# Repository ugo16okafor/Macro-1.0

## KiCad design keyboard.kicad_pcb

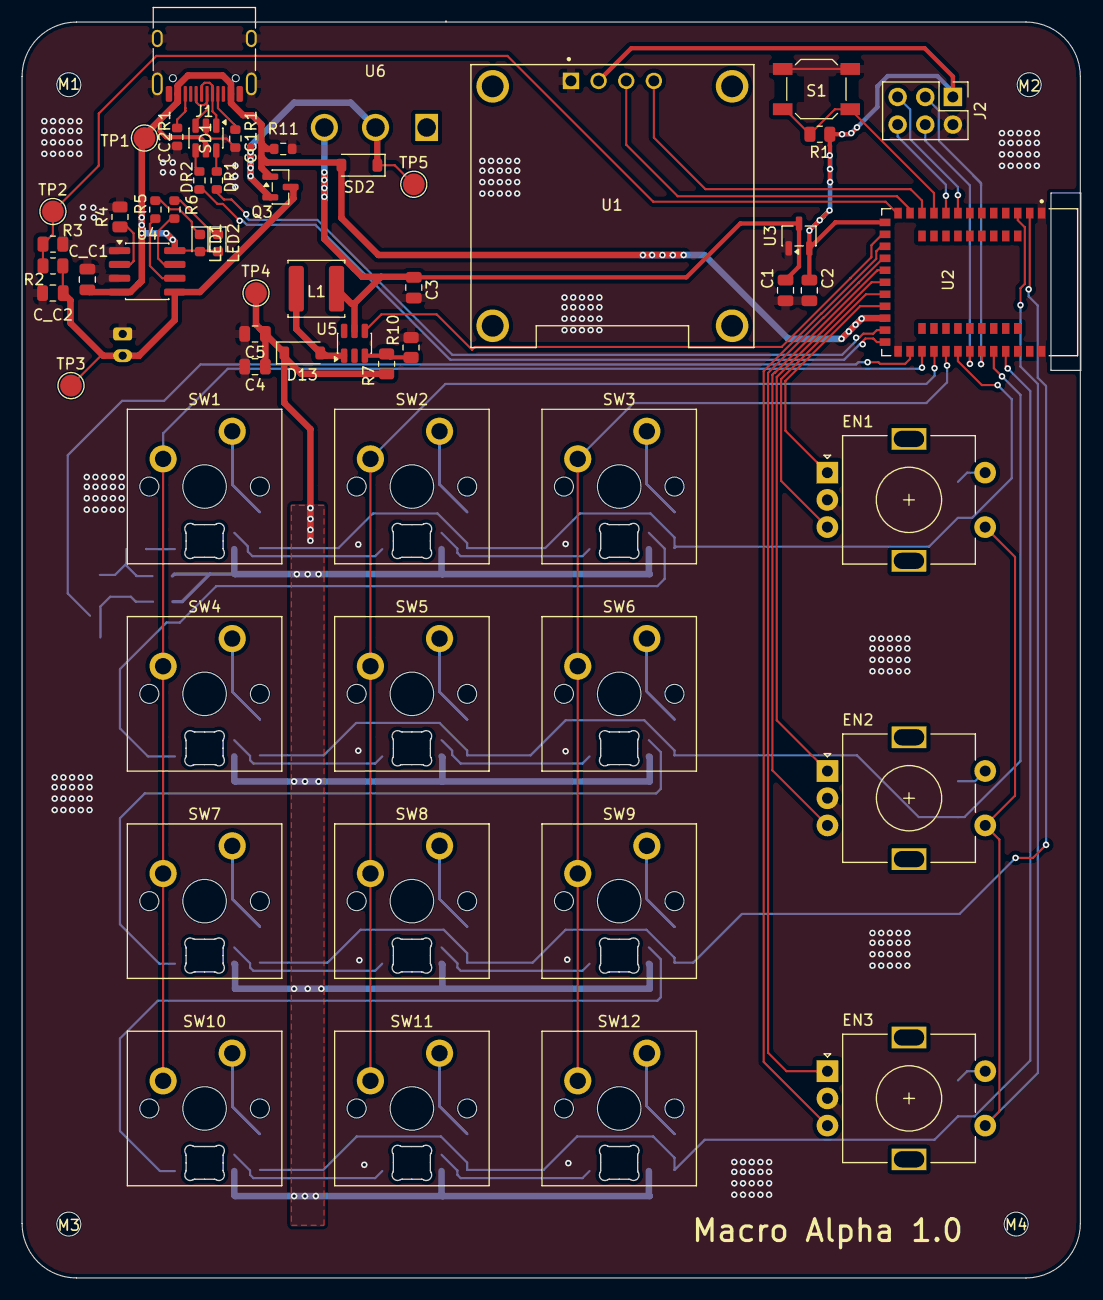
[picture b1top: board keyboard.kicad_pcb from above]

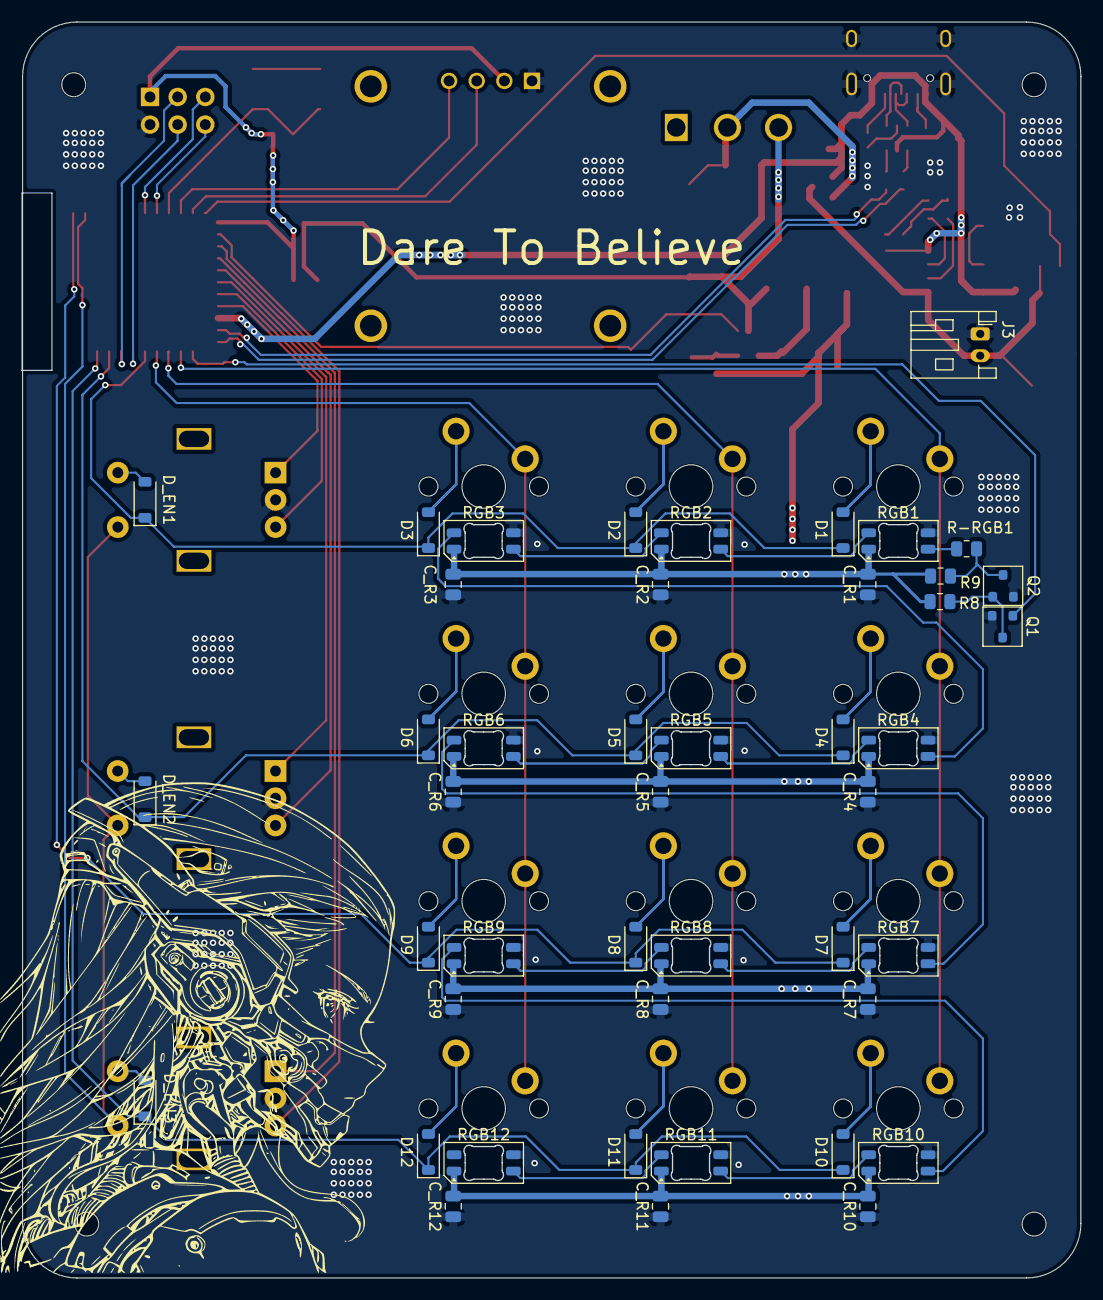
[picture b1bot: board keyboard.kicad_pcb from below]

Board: 2 copper layers, 97.3 x 115.4 mm, 105 parts (45 on the bottom side), 75 nets.

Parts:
C1, C2: 1uF; C_0805_2012Metric
C3, C5: 22uF; C_0805_2012Metric
C4: 10uF; C_0805_2012Metric
CC1R1, CC2R1: 5.1k; R_0603_1608Metric
C_C1, C_C2: 10uF; C_0805_2012Metric
C_R1, C_R2, C_R3, C_R4, C_R5, C_R6, C_R7, C_R8, C_R9, C_R10, C_R11, C_R12: 100nF; C_0805_2012Metric
D1, D2, D3, D4, D5, D6, D7, D8, D9, D10, D11, D12: D; D_SOD-123
D13: D_Schottky; D_SOD-123
DR1, DR2: 27R; R_0603_1608Metric
D_EN1, D_EN2, D_EN3: D; D_SOD-123
EN1, EN2, EN3: RotaryEncoder_Switch; RotaryEncoder_Alps_EC11E-Switch_Vertical_H20mm
J1: USB_C_Receptacle_USB2.0_16P; USB_C_Receptacle_HRO_TYPE-C-31-M-12
J2: Conn_02x06_Odd_Even; PinHeader_2x03_P2.54mm_Vertical
J3: Conn_01x02_Socket; JST_PH_S2B-PH-K_1x02_P2.00mm_Horizontal
L1: 4.7uH; L_APV_ANR5020
LED1, LED2: LED; LED_0603_1608Metric
M1, M2, M3, M4: MountingHole; MountingHole_2.2mm_M2
Q1, Q2: BSS138; SOT-23
Q3: SI2301CDS-T1-GE3; SOT-23
R1, R8, R9, R10: 10k; R_0805_2012Metric
R2: 806k; R_0805_2012Metric
R3: 2M; R_0805_2012Metric
R4: 1.2k; R_0805_2012Metric
R5, R6: 1k; R_0603_1608Metric
R7: 75k; R_0805_2012Metric
R11: 100kΩ; R_0603_1608Metric
R-RGB1: 470; R_0805_2012Metric
RGB1, RGB2, RGB3, RGB4, RGB5, RGB6, RGB7, RGB8, RGB9, RGB10, RGB11, RGB12: WS2812B; LED_SK6812MINI-E_3.2x2.8mm_P1.5mm_ReverseMount
S1: Tactile Button, 160gf; SW_SPST_SKQG_WithStem
SD1: USBLC6-2SC6; SOT-23-6
SD2: 1N5819WS; D_SOD-123
SW1, SW2, SW3, SW4, SW5, SW6, SW7, SW8, SW9, SW10, SW11, SW12: SW_Push; SW_Cherry_MX_PCB_1.00u
TP1, TP2, TP3, TP4, TP5: TestPoint; TestPoint_Pad_D2.0mm
U1: DM-OLED096-636; MODULE_DM-OLED096-636
U2: HOLYIOT-18010-NRF52840; XCVR_HOLYIOT-18010-NRF52840
U3: XC6206PxxxMR; SOT-23-3
U4: TP4056; SOP-8_3.76x4.96mm_P1.27mm
U5: MT3608; SOT-23-6
U6: SW-TH_3P-P4_70_SS-12D06-G050; SW-TH_3P-P4_70_SS-12D06-G050_SS-12D06-G050_C17179521

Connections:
3v3: C2.1, J2.1, R1.1, U1.2 (VCC_IN), U2.14 (VDD_NRF), U3.2 (VO)
BATTREAD: R2.1, R3.2, TP2.1 (1_1), U2.13 (P0_05)
COL0: SW1.1, SW4.1, SW7.1, SW10.1, U2.27 (P1_00)
COL1: SW2.1, SW5.1, SW8.1, SW11.1, U2.28 (P1_03)
COL2: SW3.1, SW6.1, SW9.1, SW12.1, U2.29 (P1_01)
COL3: EN1.S1, EN2.S1, EN3.S1, U2.3 (P1_10)
EN1A: EN1.A, U2.21 (P0_18)
EN1B: EN1.B, U2.20 (P0_19)
EN2A: EN2.A, U2.19 (P0_21)
EN2B: EN2.B, U2.18 (P0_23)
EN3A: EN3.A, U2.17 (P0_12)
EN3B: EN3.B, U2.16 (P1_09)
Extra1: J2.5, U2.8 (P0_28)
Extra2: J2.6, U2.9 (P0_29)
GND: C1.2, C2.2, C3.2, C4.2, C5.2, CC1R1.2, CC2R1.1, C_C1.2, C_C2.2, C_R1.1, C_R2.1, C_R3.1, C_R4.1, C_R5.1, C_R6.1, C_R7.1, C_R8.1, C_R9.1, C_R10.1, C_R11.1, C_R12.1, EN1.C, EN2.C, EN3.C, J1.A1 (GND), J1.A12 (GND), J1.B1 (GND), J1.B12 (GND), J1.SH (SHIELD), J2.2, J3.1, Q1.2 (S), Q2.2 (S), R3.1, R4.2, R10.2, R11.1, RGB1.3 (VSS), RGB2.3 (VSS), RGB3.3 (VSS), RGB4.3 (VSS), RGB5.3 (VSS), RGB6.3 (VSS), RGB7.3 (VSS), RGB8.3 (VSS), RGB9.3 (VSS), RGB10.3 (VSS), RGB11.3 (VSS), RGB12.3 (VSS), S1.2, SD1.2 (VN), U1.1 (GND), U2.1 (GND), U2.25 (GND), U2.37 (GND), U3.1 (GND), U4.1 (TEMP), U4.3 (GND), U5.2 (GND)
unnamed: D1.2 (A), SW1.2
unnamed: D2.2 (A), SW2.2
unnamed: D3.2 (A), SW3.2
unnamed: D4.2 (A), SW4.2
unnamed: D5.2 (A), SW5.2
unnamed: D6.2 (A), SW6.2
unnamed: D7.2 (A), SW7.2
unnamed: D8.2 (A), SW8.2
unnamed: D9.2 (A), SW9.2
unnamed: D10.2 (A), SW10.2
unnamed: D11.2 (A), SW11.2
unnamed: D12.2 (A), SW12.2
unnamed: D13.2 (A), L1.2, U5.1 (SW)
unnamed: D_EN1.2 (A), EN1.S2
unnamed: D_EN2.2 (A), EN2.S2
unnamed: D_EN3.2 (A), EN3.S2
unnamed: DR1.2, SD1.6 (L1)
unnamed: DR2.2, SD1.4 (L2)
unnamed: CC1R1.1, J1.A5 (CC1)
unnamed: CC2R1.2, J1.B5 (CC2)
unnamed: J1.A6 (D+), J1.B6 (D+), SD1.3 (L2)
unnamed: J1.A7 (D-), J1.B7 (D-), SD1.1 (L1)
unnamed: LED1.1 (K), R5.1
unnamed: LED2.1 (K), R6.1
unnamed: Q1.3 (D), Q2.1 (G), R8.2
unnamed: R-RGB1.2, RGB1.4 (DIN)
unnamed: RGB1.2 (DOUT), RGB2.4 (DIN)
unnamed: RGB2.2 (DOUT), RGB3.4 (DIN)
unnamed: RGB3.2 (DOUT), RGB4.4 (DIN)
unnamed: RGB4.2 (DOUT), RGB5.4 (DIN)
unnamed: RGB5.2 (DOUT), RGB6.4 (DIN)
unnamed: RGB6.2 (DOUT), RGB7.4 (DIN)
unnamed: RGB7.2 (DOUT), RGB8.4 (DIN)
unnamed: RGB8.2 (DOUT), RGB9.4 (DIN)
unnamed: RGB9.2 (DOUT), RGB10.4 (DIN)
unnamed: RGB10.2 (DOUT), RGB11.4 (DIN)
unnamed: RGB11.2 (DOUT), RGB12.4 (DIN)
unnamed: R6.2, U4.7 (CHRG#)
unnamed: R4.1, U4.2 (PROG)
unnamed: R5.2, U4.6 (STDBY#)
unnamed: R7.2, R10.1, U5.3 (FB)
RGB_DATA 3v: Q1.1 (G), U2.26 (P0_22)
RGB_DATA 5v: Q2.3 (D), R9.2, R-RGB1.1
RGB_EN: U2.15 (P0_07), U5.4 (EN)
ROW0: D1.1 (K), D2.1 (K), D3.1 (K), D_EN1.1 (K), U2.30 (P1_02)
ROW1: D4.1 (K), D5.1 (K), D6.1 (K), D_EN2.1 (K), U2.33 (P1_04)
ROW2: D7.1 (K), D8.1 (K), D9.1 (K), U2.2 (P1_11)
ROW3: D10.1 (K), D11.1 (K), D12.1 (K), D_EN3.1 (K), U2.34 (P1_06)
RST: R1.2, S1.1, U2.10 (P0_30)
SCL: U1.3 (SCL), U2.12 (P0_04)
SDA: U1.4 (SDA), U2.11 (P0_31)
SWDCLK: J2.4, U2.31 (SWDCLK)
SWDIO: J2.3, U2.32 (SWDIO)
VBAT: C_C2.1, J3.2, Q3.3 (D), R2.2, TP3.1 (1_1), U4.5 (BAT)
VBUS: C_C1.1, J1.A4 (VBUS), J1.A9 (VBUS), J1.B4 (VBUS), J1.B9 (VBUS), LED1.2 (A), LED2.2 (A), Q3.1 (G), R11.2, SD1.5 (VP), SD2.2, TP1.1 (1_1), U2.22 (VBUS), U4.4 (VCC), U4.8 (CE)
VCC_RGB: C4.1, C5.1, C_R1.2, C_R2.2, C_R3.2, C_R4.2, C_R5.2, C_R6.2, C_R7.2, C_R8.2, C_R9.2, C_R10.2, C_R11.2, C_R12.2, D13.1 (K), R7.1, R8.1, R9.1, RGB1.1 (VDD), RGB2.1 (VDD), RGB3.1 (VDD), RGB4.1 (VDD), RGB5.1 (VDD), RGB6.1 (VDD), RGB7.1 (VDD), RGB8.1 (VDD), RGB9.1 (VDD), RGB10.1 (VDD), RGB11.1 (VDD), RGB12.1 (VDD), TP4.1 (1_1)
VSYS: C1.1, C3.1, L1.1, U3.3 (VI), U5.5 (IN), U6.3
VSYS_SW: Q3.2 (S), SD2.1, TP5.1 (1_1), U6.2
d+: DR2.1, U2.24 (DP)
d-: DR1.1, U2.23 (DN)
